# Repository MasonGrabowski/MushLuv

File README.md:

# MushLuv
Teensy 4.1 based data logger for indoor mushroom cultivation ("RWM" Final Project)

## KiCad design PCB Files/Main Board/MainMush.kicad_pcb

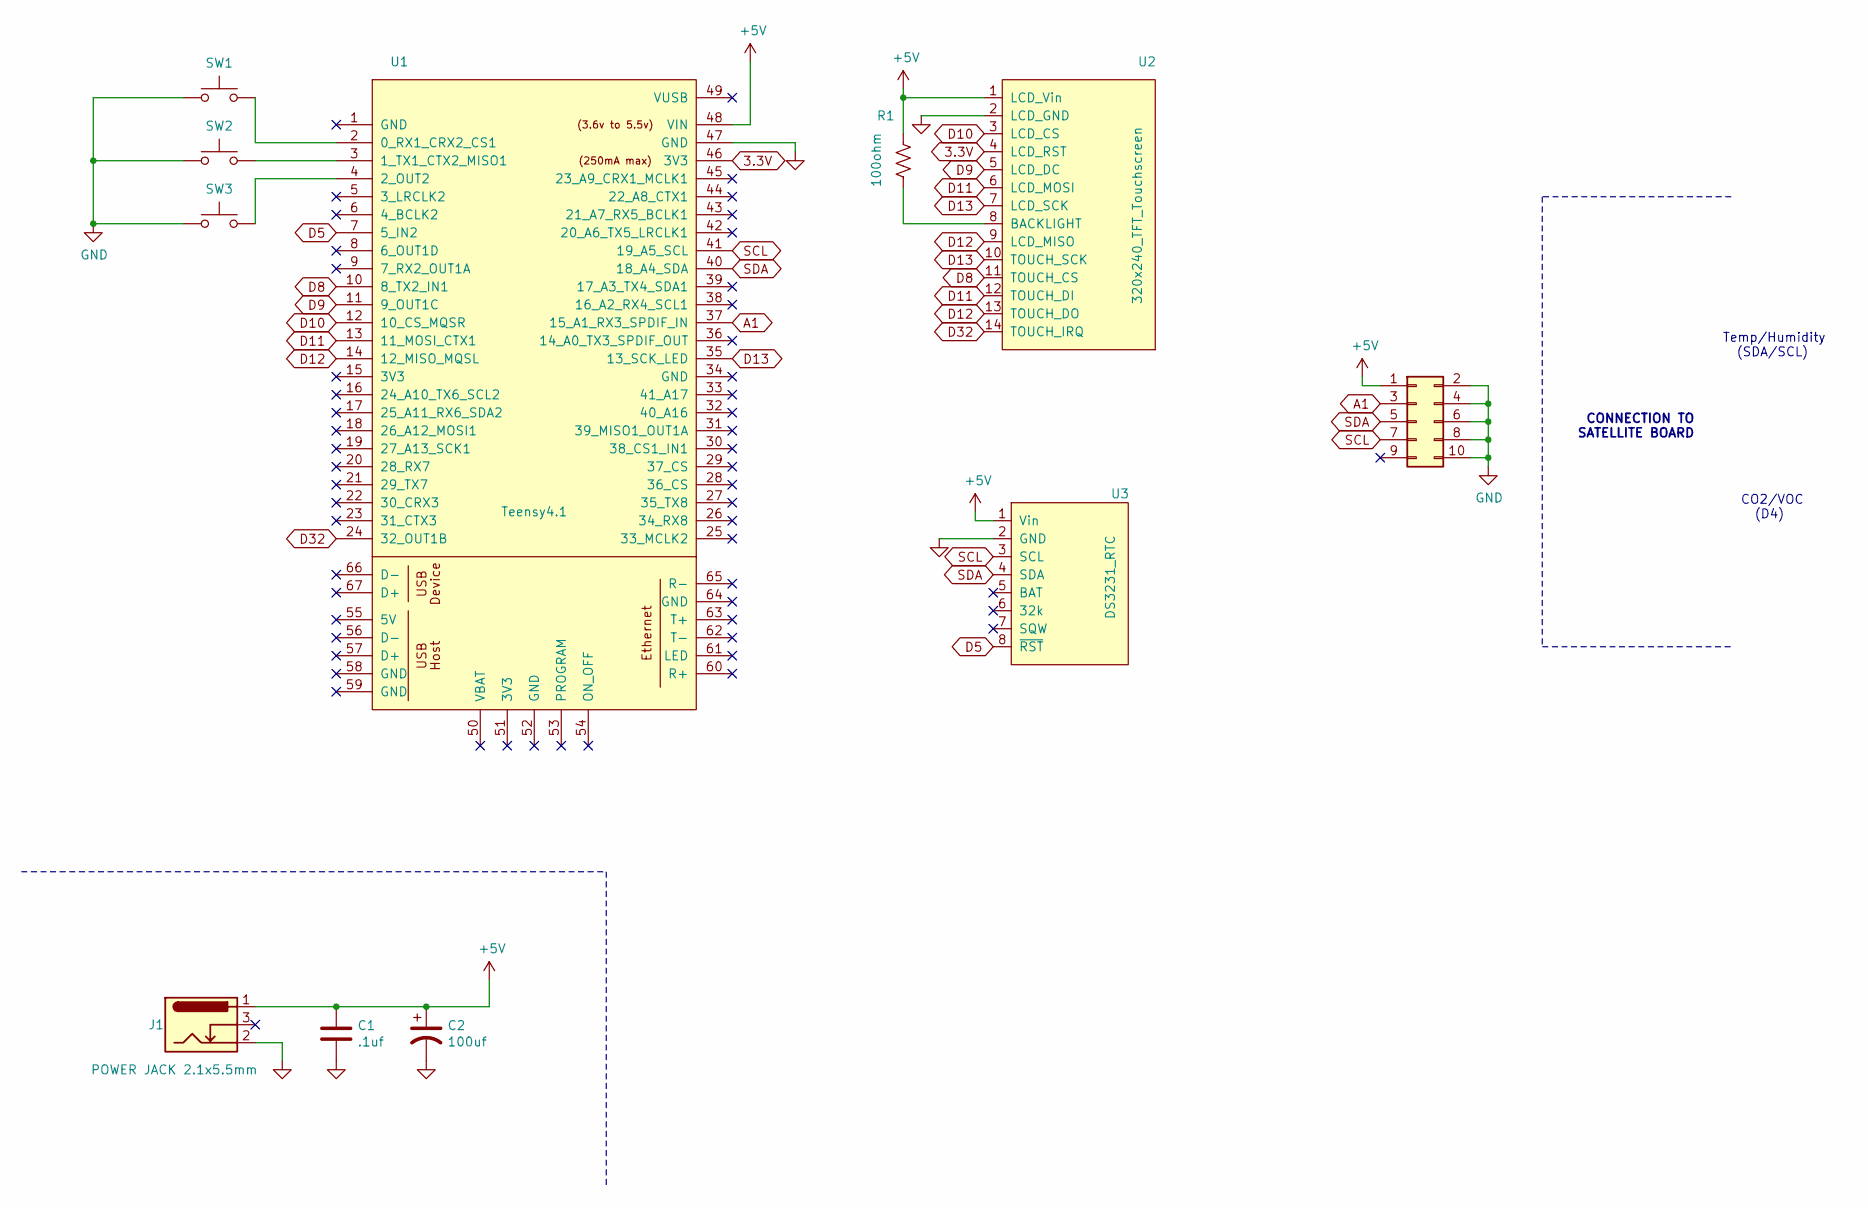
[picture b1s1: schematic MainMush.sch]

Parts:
C1: .1uf; C_Disc_D5.0mm_W2.5mm_P2.50mm
C2: 100uf; CP_Radial_D6.3mm_P2.50mm
J1: POWER JACK 2.1x5.5mm; BarrelJack_dummyBIGholes
J2: Conn_02x05_Odd_Even; 10pin_ribboncable_connector
R1: 100ohm; R_Axial_DIN0207_L6.3mm_D2.5mm_P10.16mm_Horizontal
SW1, SW2, SW3: SW_Push; SW_PUSH_6mm_H7.3mm
U1: Teensy4.1; Teensy41
U2: 320x240_TFT_Touchscreen; 320x240 TFT Touchscreen
U3: DS3231_RTC; ds3231

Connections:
3.3V: U1.46 (3V3), U2.4 (LCD_RST)
+5V: C1.1, C2.1, J1.1, J2.1, R1.1, U1.48 (VIN), U2.1 (LCD_Vin), U3.1 (Vin)
A1: J2.3, U1.37 (15_A1_RX3_SPDIF_IN)
D5: U1.7 (5_IN2), U3.8 (~RST)
D8: U1.10 (8_TX2_IN1), U2.11 (TOUCH_CS)
D9: U1.11 (9_OUT1C), U2.5 (LCD_DC)
D10: U1.12 (10_CS_MQSR), U2.3 (LCD_CS)
D11: U1.13 (11_MOSI_CTX1), U2.6 (LCD_MOSI), U2.12 (TOUCH_DI)
D12: U1.14 (12_MISO_MQSL), U2.9 (LCD_MISO), U2.13 (TOUCH_DO)
D13: U1.35 (13_SCK_LED), U2.7 (LCD_SCK), U2.10 (TOUCH_SCK)
D32: U1.24 (32_OUT1B), U2.14 (TOUCH_IRQ)
GND: C1.2, C2.2, J1.2, J2.2, J2.4, J2.6, J2.8, J2.10, SW1.1, SW2.1, SW3.1, U1.47 (GND), U2.2 (LCD_GND), U3.2 (GND)
unnamed: R1.2, U2.8 (BACKLIGHT)
unnamed: SW1.2, U1.2 (0_RX1_CRX2_CS1)
unnamed: SW2.2, U1.3 (1_TX1_CTX2_MISO1)
unnamed: SW3.2, U1.4 (2_OUT2)
SCL: J2.7, U1.41 (19_A5_SCL), U3.3 (SCL)
SDA: J2.5, U1.40 (18_A4_SDA), U3.4 (SDA)

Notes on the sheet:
CONNECTION TO SATELLITE BOARD
Temp/Humidity (SDA/SCL)
CO2/VOC (D4)

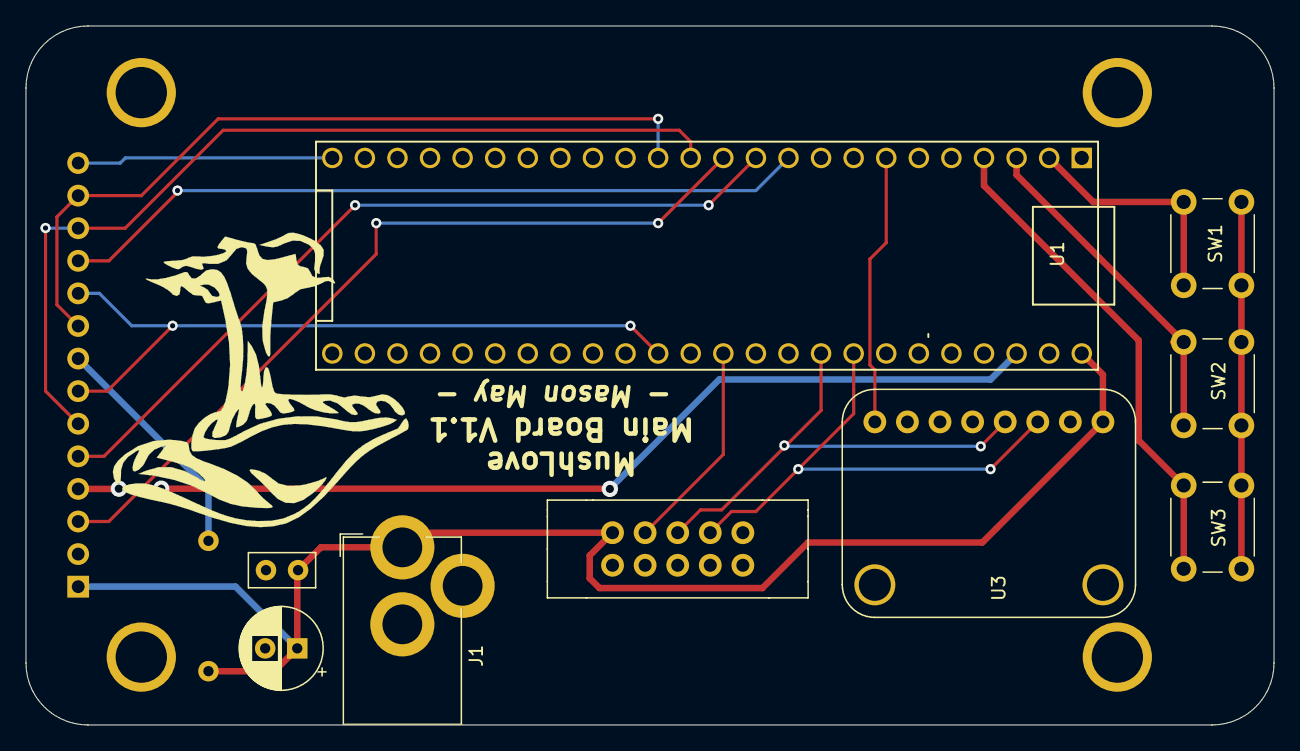
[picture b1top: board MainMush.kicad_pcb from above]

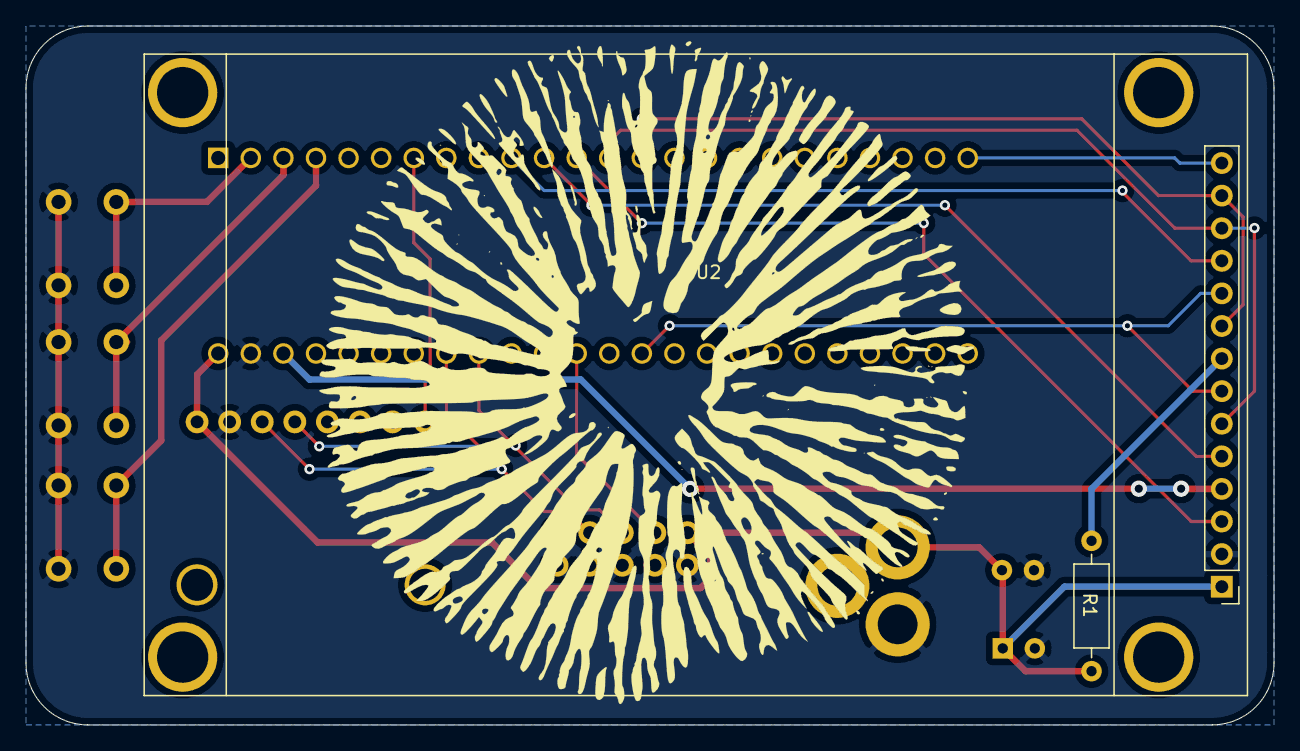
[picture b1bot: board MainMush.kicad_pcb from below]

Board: 2 copper layers, 97.3 x 54.5 mm, 11 parts (2 on the bottom side), 18 nets.

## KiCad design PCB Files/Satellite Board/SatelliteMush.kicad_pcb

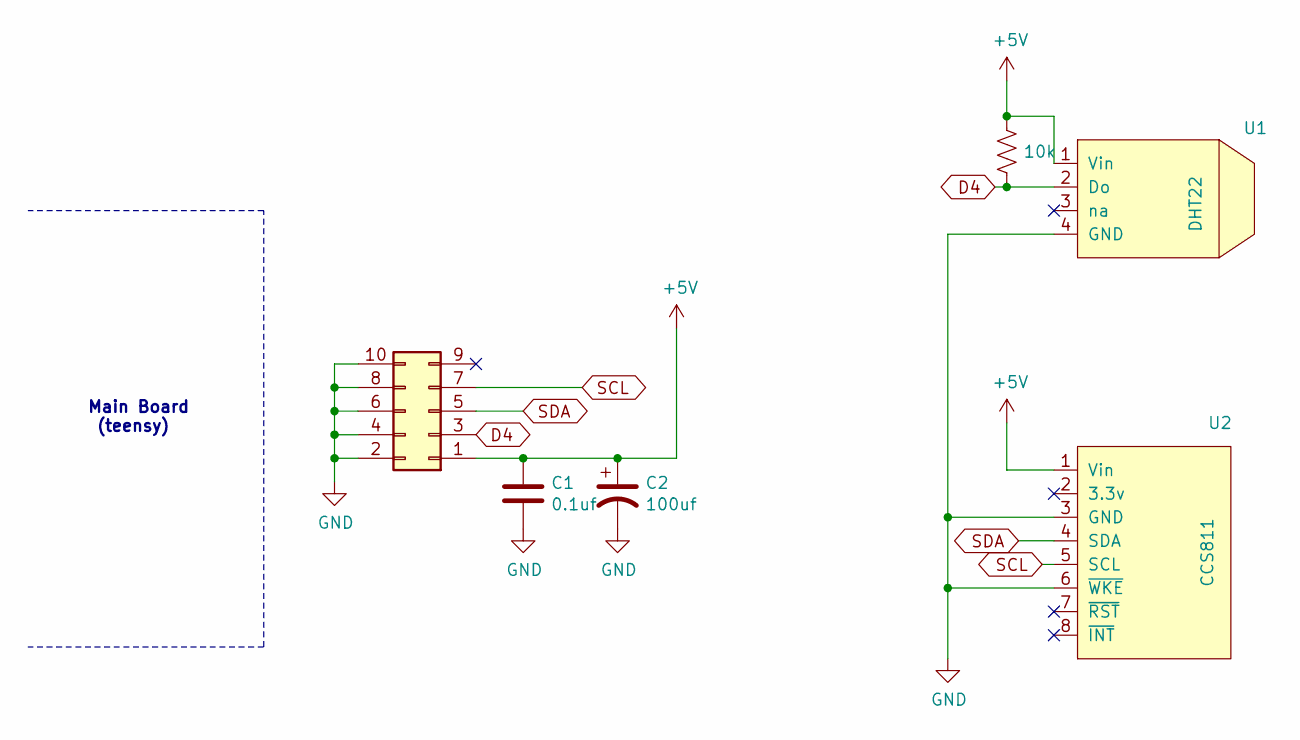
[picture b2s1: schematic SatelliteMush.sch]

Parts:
C1: 0.1uf; C_Disc_D5.0mm_W2.5mm_P2.50mm
C2: 100uf; CP_Radial_D6.3mm_P2.50mm
J1: Conn_02x05_Odd_Even; 10pin_ribboncable_connector
R1: 10k; resistor
U1: DHT22
U2: CCS811

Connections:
+5V: C1.1, C2.1, J1.1, R1.1, U1.1 (Vin), U2.1 (Vin)
D4: J1.3, R1.2, U1.2 (Do)
GND: C1.2, C2.2, J1.2, J1.4, J1.6, J1.8, J1.10, U1.4 (GND), U2.3 (GND), U2.6 (~WKE)
SCL: J1.7, U2.5 (SCL)
SDA: J1.5, U2.4 (SDA)

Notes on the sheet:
Main Board (teensy)

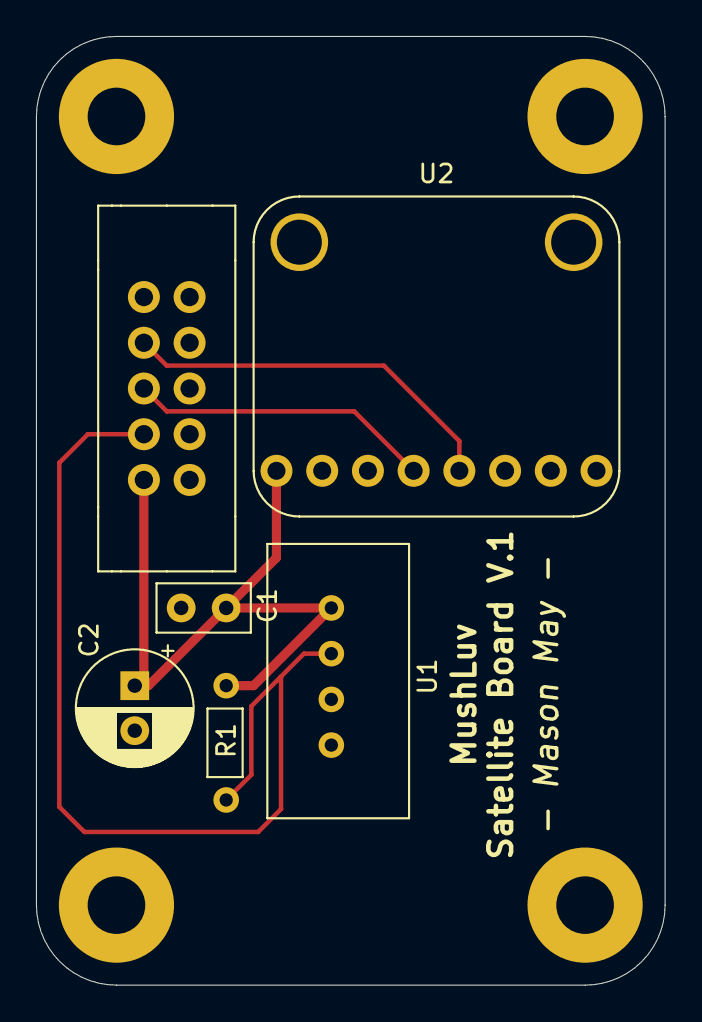
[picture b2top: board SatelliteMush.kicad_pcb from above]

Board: 2 copper layers, 34.9 x 52.7 mm, 6 parts (0 on the bottom side), 5 nets.

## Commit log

2020-12-18 adding photos folder
2020-12-18 (re)adding photos
2020-12-18 PCB files
